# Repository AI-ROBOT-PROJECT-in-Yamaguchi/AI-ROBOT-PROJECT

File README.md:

# はじめに

大学のおもしろプロジェクト2019から資金援助を受け、AIを用いたホビーロボットを制作するプロジェクト

# ファイル構成

* USER
USER側ロボットのプログラム。ps4コントローラの設定など

* AI
AI側のプログラム。深層学習など

* common
共通のプログラム。ARやスマートスピーカーなど

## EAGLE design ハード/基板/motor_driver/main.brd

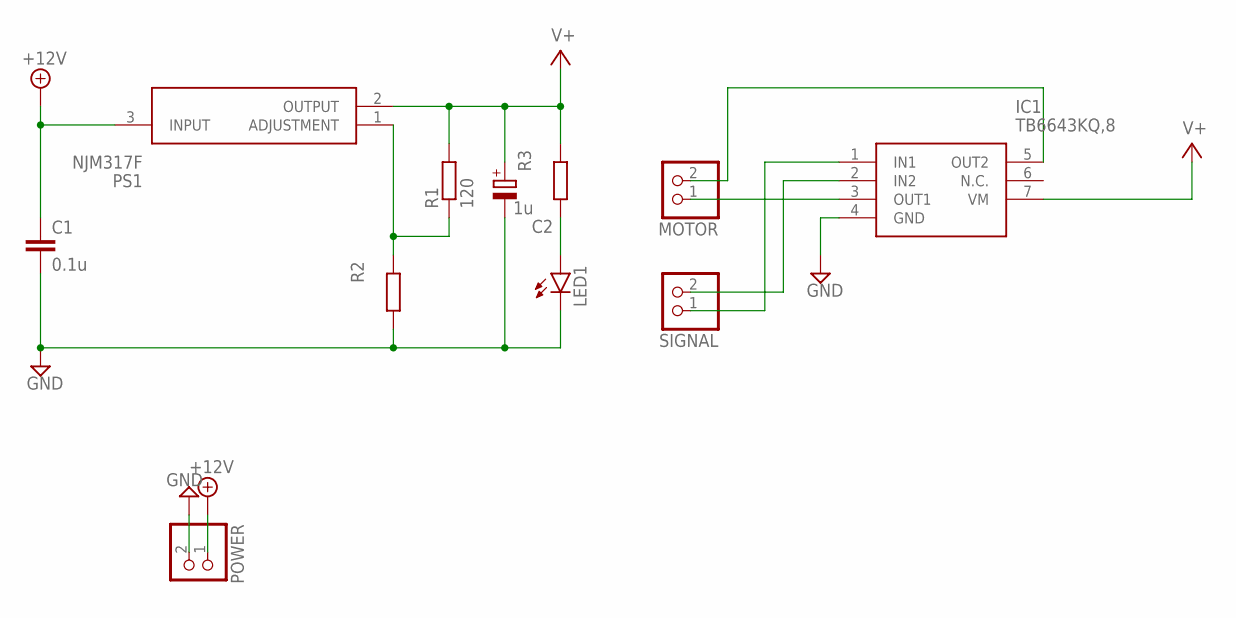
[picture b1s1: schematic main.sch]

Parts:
C1: 0.1u; C050-024X044
C2: 1u; E2,5-7
IC1: TB6643KQ,8; HSIP7-P-2.54A
LED1: LED5MM
MOTOR: PINHD-1X2; 1X02
POWER: PINHD-1X2; 1X02
PS1: NJM317F; TO254P500X1000X2170-3P
R1: 120; 0207/10
R2, R3: R-EU_0207/10; 0207/10
SIGNAL: PINHD-1X2; 1X02

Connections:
+12V: C1.1, POWER.1, PS1.3 (INPUT)
GND: C1.2, C2.-, IC1.4 (GND), LED1.K (C), POWER.2, R2.1
unnamed: IC1.3 (OUT1), MOTOR.1
unnamed: IC1.5 (OUT2), MOTOR.2
unnamed: PS1.1 (ADJUSTMENT), R1.1, R2.2
unnamed: IC1.2 (IN2), SIGNAL.2
unnamed: IC1.1 (IN1), SIGNAL.1
unnamed: LED1.A, R3.1
V+: C2.+, IC1.7 (VM), PS1.2 (OUTPUT), R1.2, R3.2

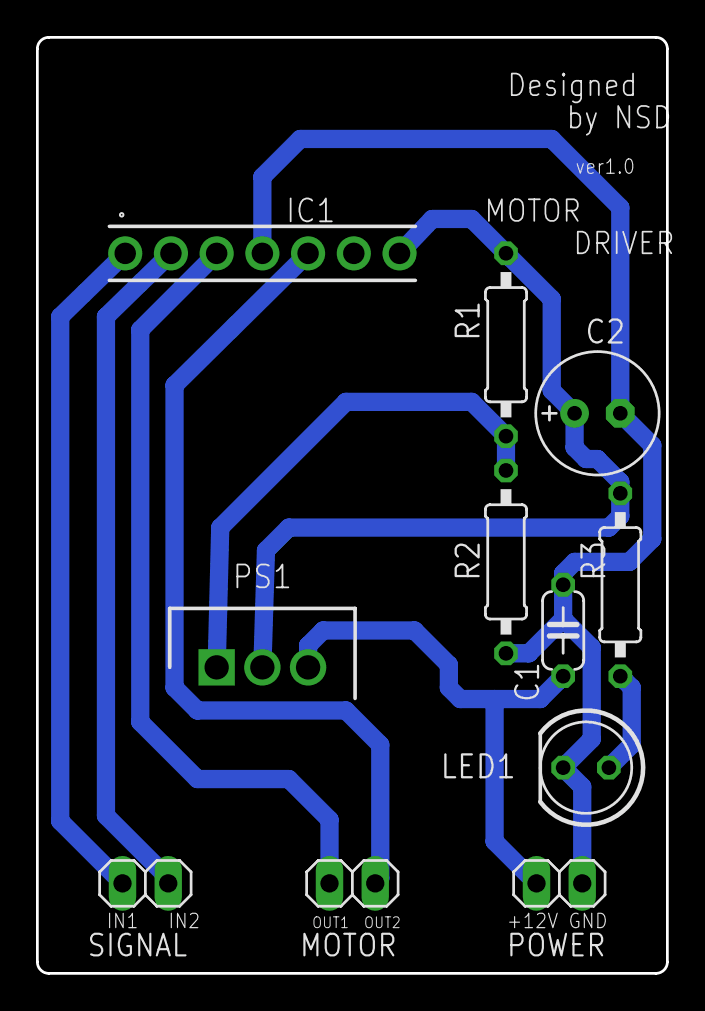
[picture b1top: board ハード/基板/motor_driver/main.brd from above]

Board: 2 copper layers, 35.0 x 52.0 mm, 11 parts (0 on the bottom side), 9 nets.

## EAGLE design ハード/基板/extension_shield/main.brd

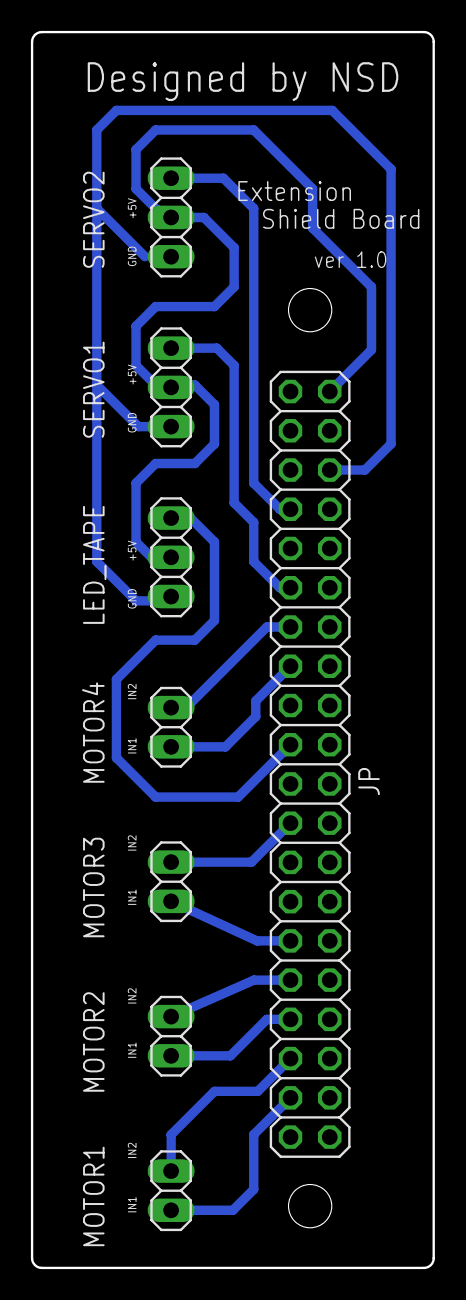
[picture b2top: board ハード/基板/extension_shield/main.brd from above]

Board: 2 copper layers, 26.0 x 80.0 mm, 8 parts (0 on the bottom side), 13 nets.

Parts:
JP: 2X20
LED_TAPE: 1X03
MOTOR1, MOTOR2, MOTOR3, MOTOR4: 1X02
SERVO1, SERVO2: 1X03

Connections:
5V: JP.2, LED_TAPE.2, SERVO1.2, SERVO2.2
GND: JP.6, LED_TAPE.1, SERVO1.1, SERVO2.1
unnamed: JP.19, LED_TAPE.3
unnamed: JP.37, MOTOR1.1
unnamed: JP.35, MOTOR1.2
unnamed: JP.33, MOTOR2.1
unnamed: JP.31, MOTOR2.2
unnamed: JP.29, MOTOR3.1
unnamed: JP.23, MOTOR3.2
unnamed: JP.13, MOTOR4.2
unnamed: JP.15, MOTOR4.1
unnamed: JP.7, SERVO2.3
unnamed: JP.11, SERVO1.3

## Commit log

2019-06-29 READMEを追加
2019-11-11 jetson nanoやラズパイにつかえる拡張シールドを設計
2019-11-11 モータードライバーを設計
2019-11-11 文字を追加した
2019-11-11 文字を追加し、デザインを調整
2020-02-05 ps4コントローラの制御コードサンプルを追加
2020-02-05 get left joystick value
2020-02-06 output joystick angle
2020-02-06 add input data assign comment
2020-02-06 smartspeakerブランチの作成
2020-02-06 add rotate command
2020-02-07 gTTSを使って文字列を音声ファイルに変換するサーバー作成
2020-02-07 text_to_speech.py 削除
2020-02-07 googleHomeをしゃべらせるプログラムghtts作成
2020-02-09 READMEにディレクトリ構成を追加
2020-02-12 ディレクトリ作成用の空ファイルを削除
2020-02-12 herokuにデプロイできるようにした。
2020-02-13 add automatic start function
2020-02-18 add 4 wheel move function
2020-02-27 add meve rotate brake function
2020-03-02 add change speed func and change LRjoystick
2020-03-04 change order bluetooth and gpio
2020-03-16 webARのサンプルコードを追加
2020-03-18 add pid function
2020-03-18 puch square button and vibration
2020-03-18 speed change button push and vibration
2020-03-25 ttsServer ドキュメント追加
2020-03-25 ghttsを音声ファイルを再生するだけのghplayに変更した。
2020-03-25 ghplay ドキュメントを追加
2020-03-27 設定項目をghconfig.pyに分離
2020-03-27 ghconfigに関する記述をreadme.mdに追加
2020-03-27 ghplay.py 関数として呼び出せるようにした。
2020-03-27 ghtalk.py 実装
2020-04-12 ps4コントローラを振動させるためのスクリプトを追加
2020-04-13 Three.jsで背景を設定することに成功した。(未調整)
